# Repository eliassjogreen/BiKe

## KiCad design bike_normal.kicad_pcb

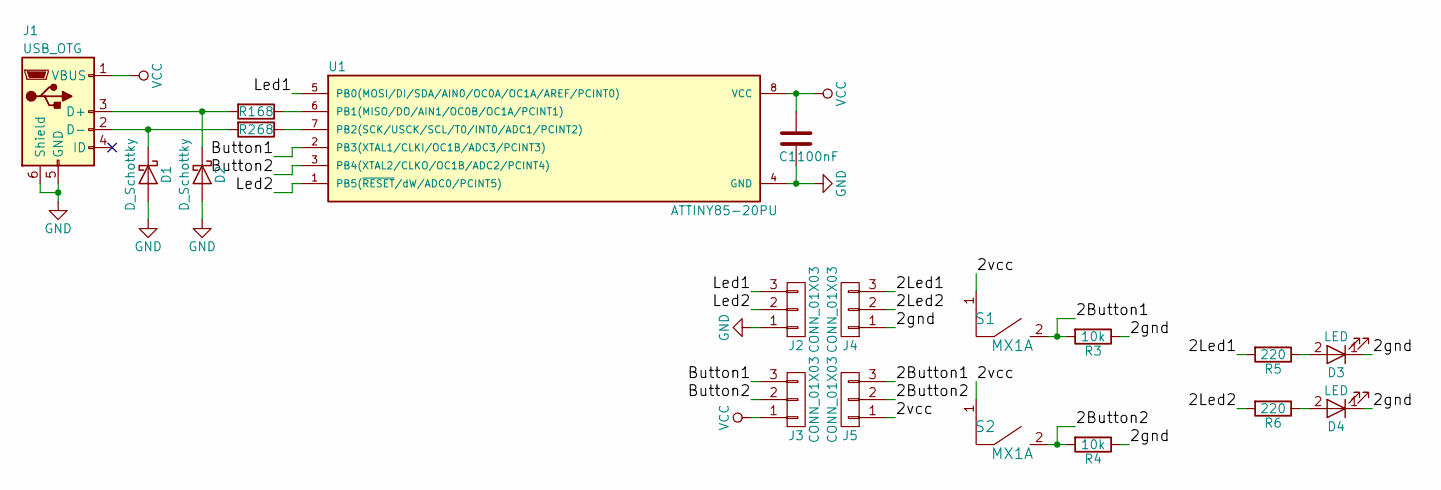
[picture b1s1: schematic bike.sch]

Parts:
C1: 100nF; C_0805_HandSoldering
D1, D2: D_Schottky; D_DO-35_SOD27_P7.62mm_Horizontal
D3, D4: LED; MX1A-led
J1: USB_OTG; USB_miniB_hirose_5ST_hand
J2, J3, J4, J5: CONN_01X03; Pin_Header_Straight_1x03_Pitch2.54mm
R1, R2: 68; R_0805_HandSoldering
R3, R4: 10k; R_0805_HandSoldering
R5, R6: 220; R_0805_HandSoldering
S1, S2: MX1A
U1: ATTINY85-20PU; DIP-8_W7.62mm

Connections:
/2Button1: J5.3, R3.2, S1.2
/2Button2: J5.2, R4.2, S2.2
/2Led1: J4.3, R5.2
/2Led2: J4.2, R6.2
/2gnd: D3.1 (K), D4.1 (K), J4.1, R3.1, R4.1
/2vcc: J5.1, S1.1, S2.1
/Button1: J3.3, U1.2 (PB3(XTAL1/CLKI/OC1B/ADC3/PCINT3))
/Button2: J3.2, U1.3 (PB4(XTAL2/CLKO/OC1B/ADC2/PCINT4))
/Led1: J2.3, U1.5 (PB0(MOSI/DI/SDA/AIN0/OC0A/OC1A/AREF/PCI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)
/Led2: J2.2, U1.1 (PB5(~RESET~/dW/ADC0/PCINT5))
GND: C1.2, D1.2 (A), D2.2 (A), J1.5 (GND), J1.6 (Shield), J2.1, U1.4 (GND)
unnamed: D1.1 (K), J1.2 (D-), R2.2
unnamed: D2.1 (K), J1.3 (D+), R1.2
unnamed: D3.2 (A), R5.1
unnamed: D4.2 (A), R6.1
unnamed: R1.1, U1.6 (PB1(MISO/DO/AIN1/OC0B/OC1A/PCINT1))
unnamed: R2.1, U1.7 (PB2(SCK/USCK/SCL/T0/INT0/ADC1/PCINT2))
VCC: C1.1, J1.1 (VBUS), J3.1, U1.8 (VCC)

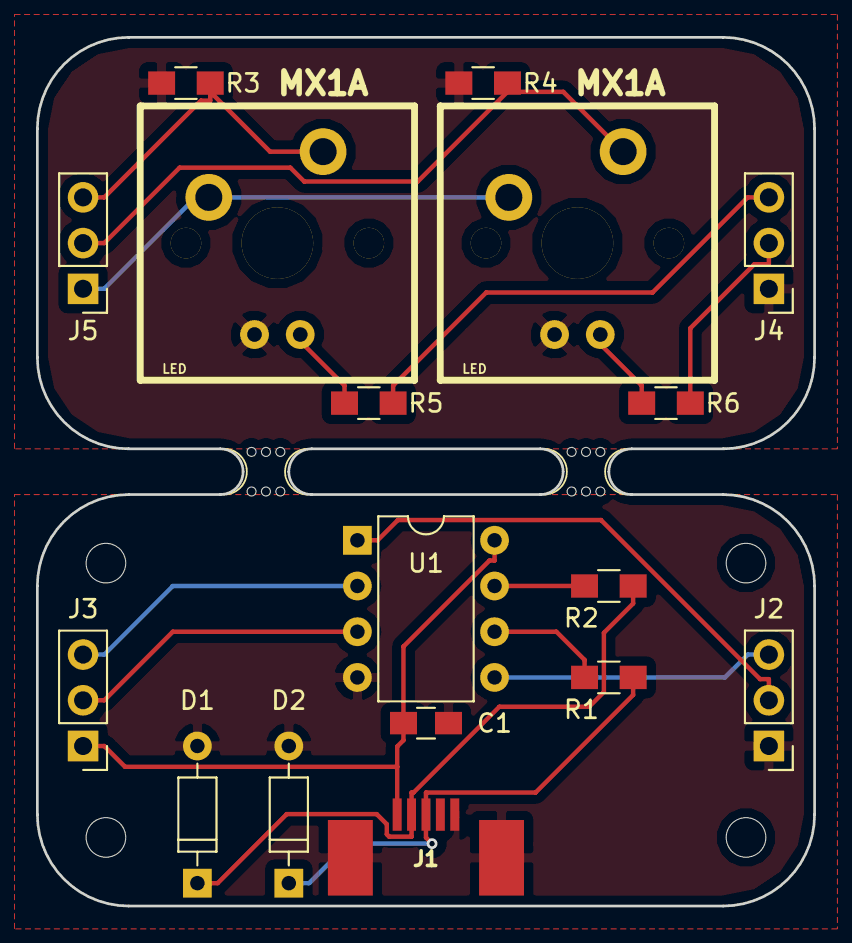
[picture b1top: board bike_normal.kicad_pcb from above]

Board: 2 copper layers, 43.2 x 48.3 mm, 25 parts (0 on the bottom side), 18 nets.

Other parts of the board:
2.2_M2_1: M2_1; MountingHole_2.2mm_M2
2.2_M2_2: M2_2; MountingHole_2.2mm_M2
2.2_M2_3: M2_3; MountingHole_2.2mm_M2
2.2_M2_4: M2_4; MountingHole_2.2mm_M2
mouse-bite-2.54mm-slot_1: VAL1; mouse-bite-2.54mm-slot
mouse-bite-2.54mm-slot_2: VAL2; mouse-bite-2.54mm-slot

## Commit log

2018-01-19 Initial commit :P
2018-01-19 Added gerbers
